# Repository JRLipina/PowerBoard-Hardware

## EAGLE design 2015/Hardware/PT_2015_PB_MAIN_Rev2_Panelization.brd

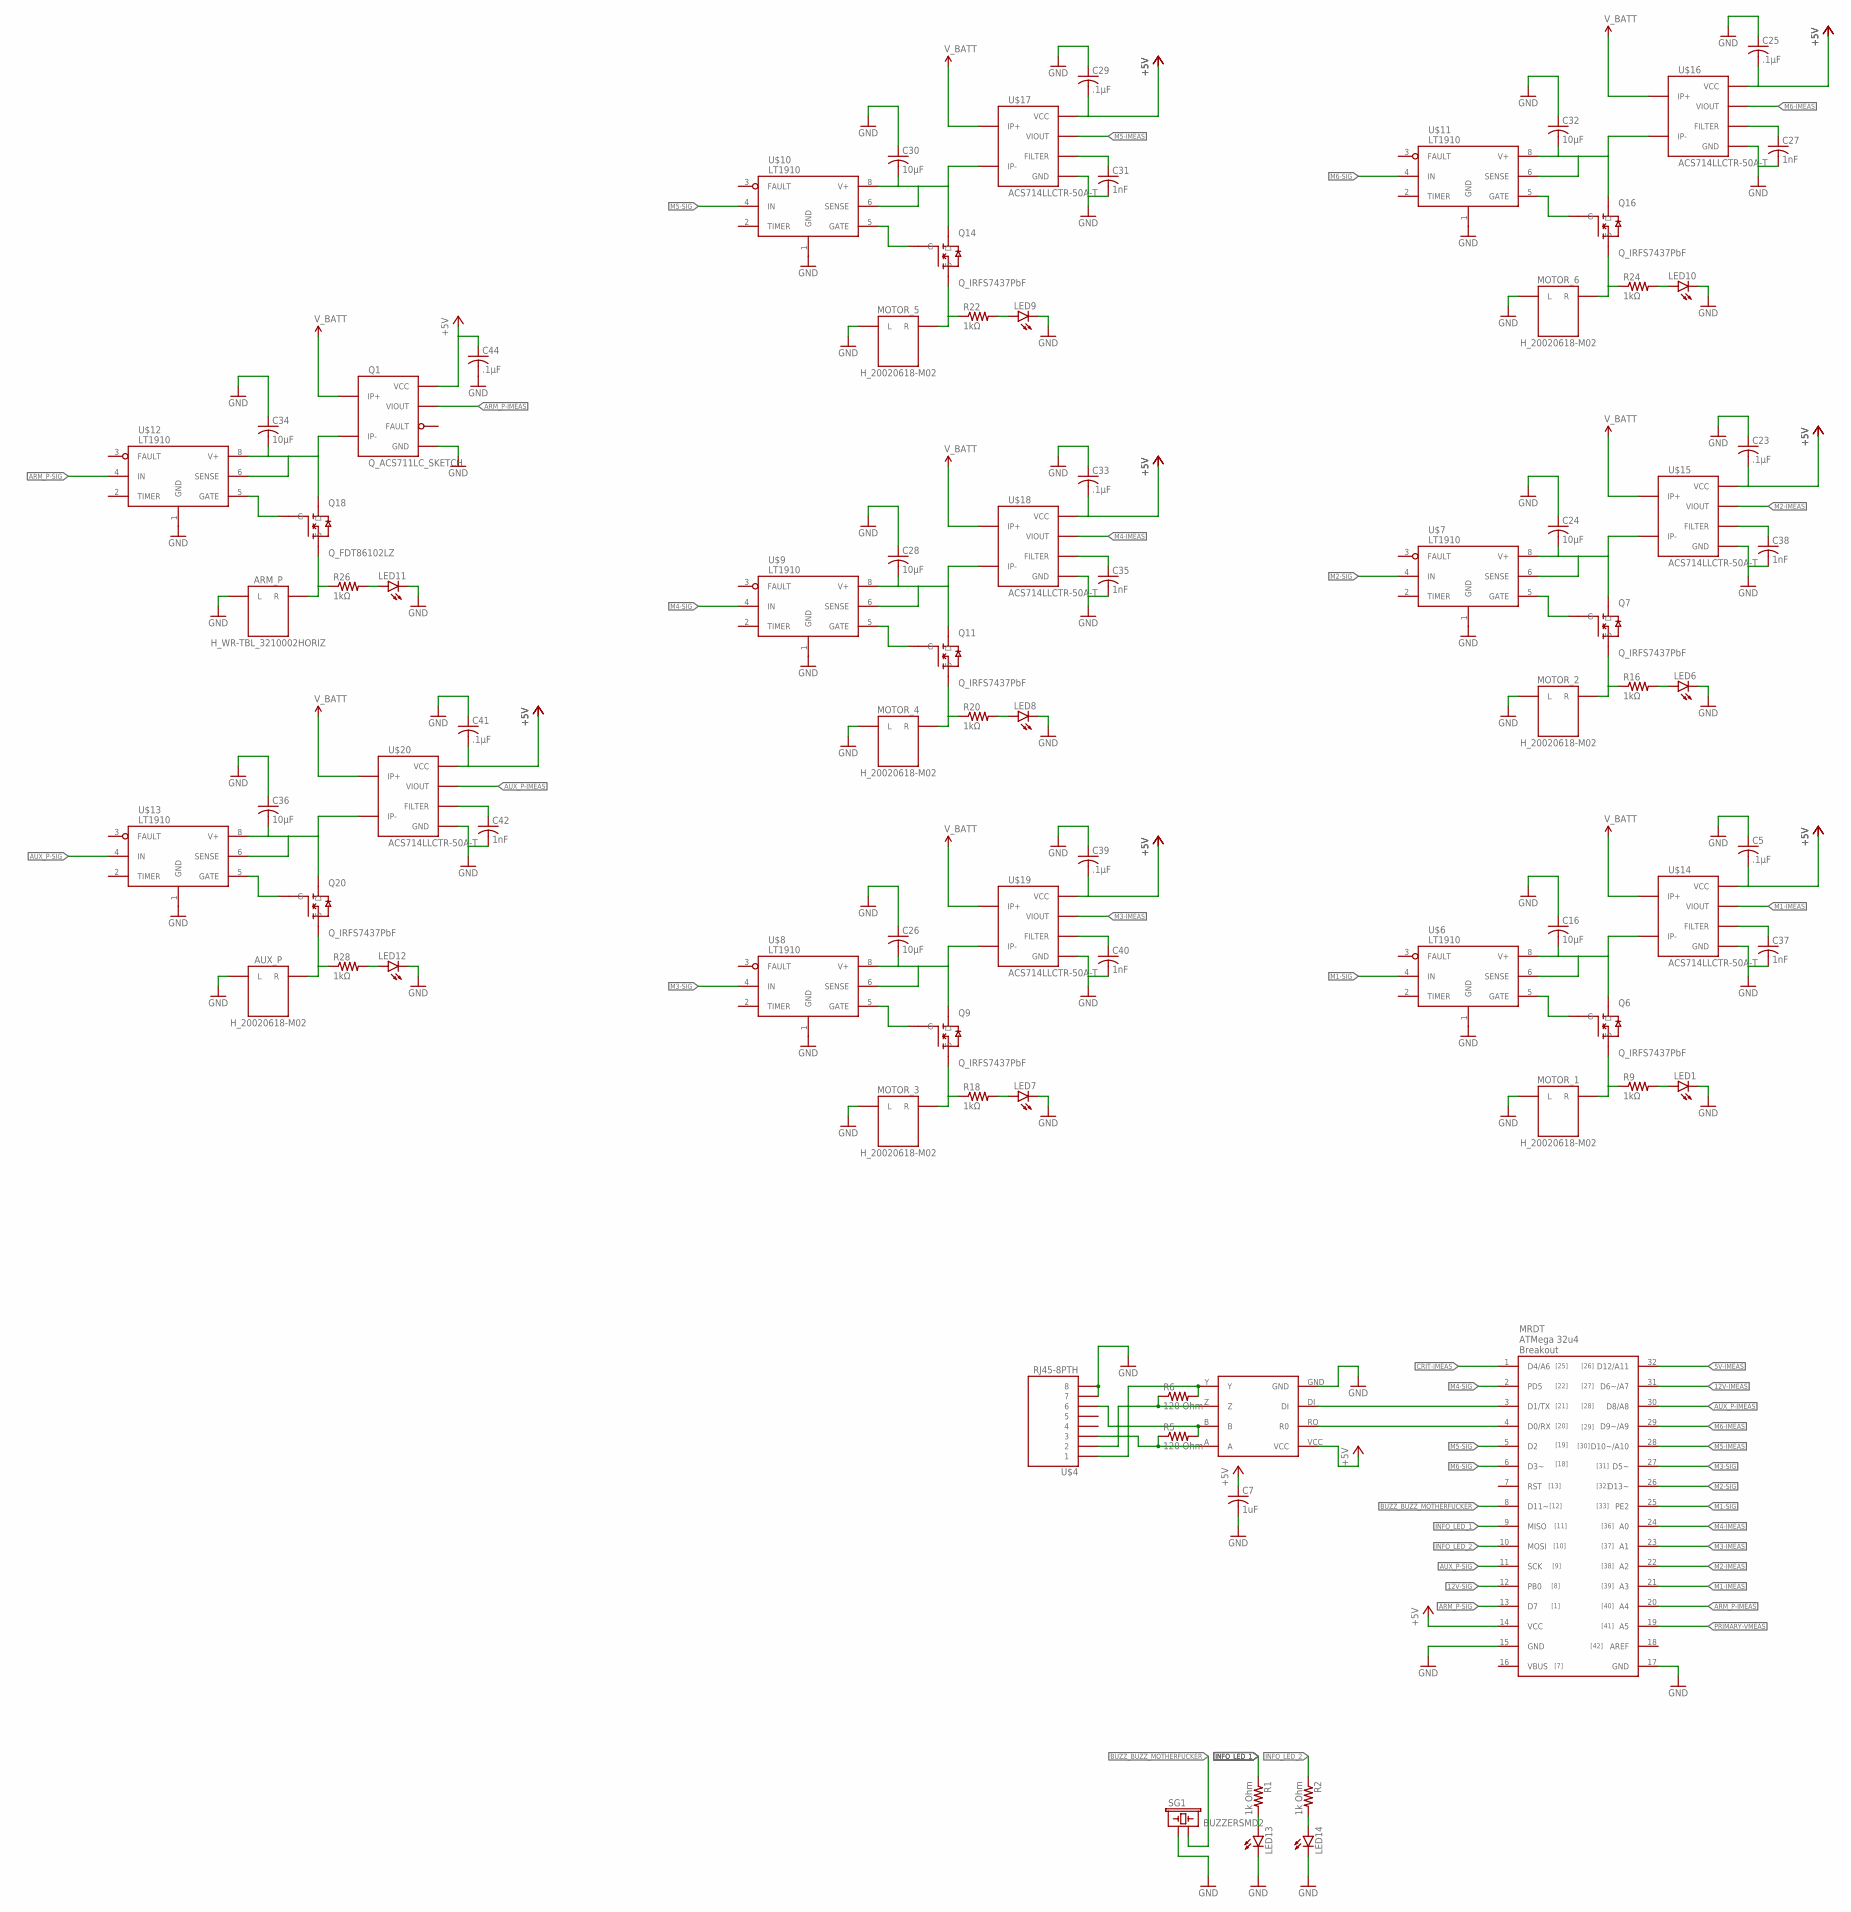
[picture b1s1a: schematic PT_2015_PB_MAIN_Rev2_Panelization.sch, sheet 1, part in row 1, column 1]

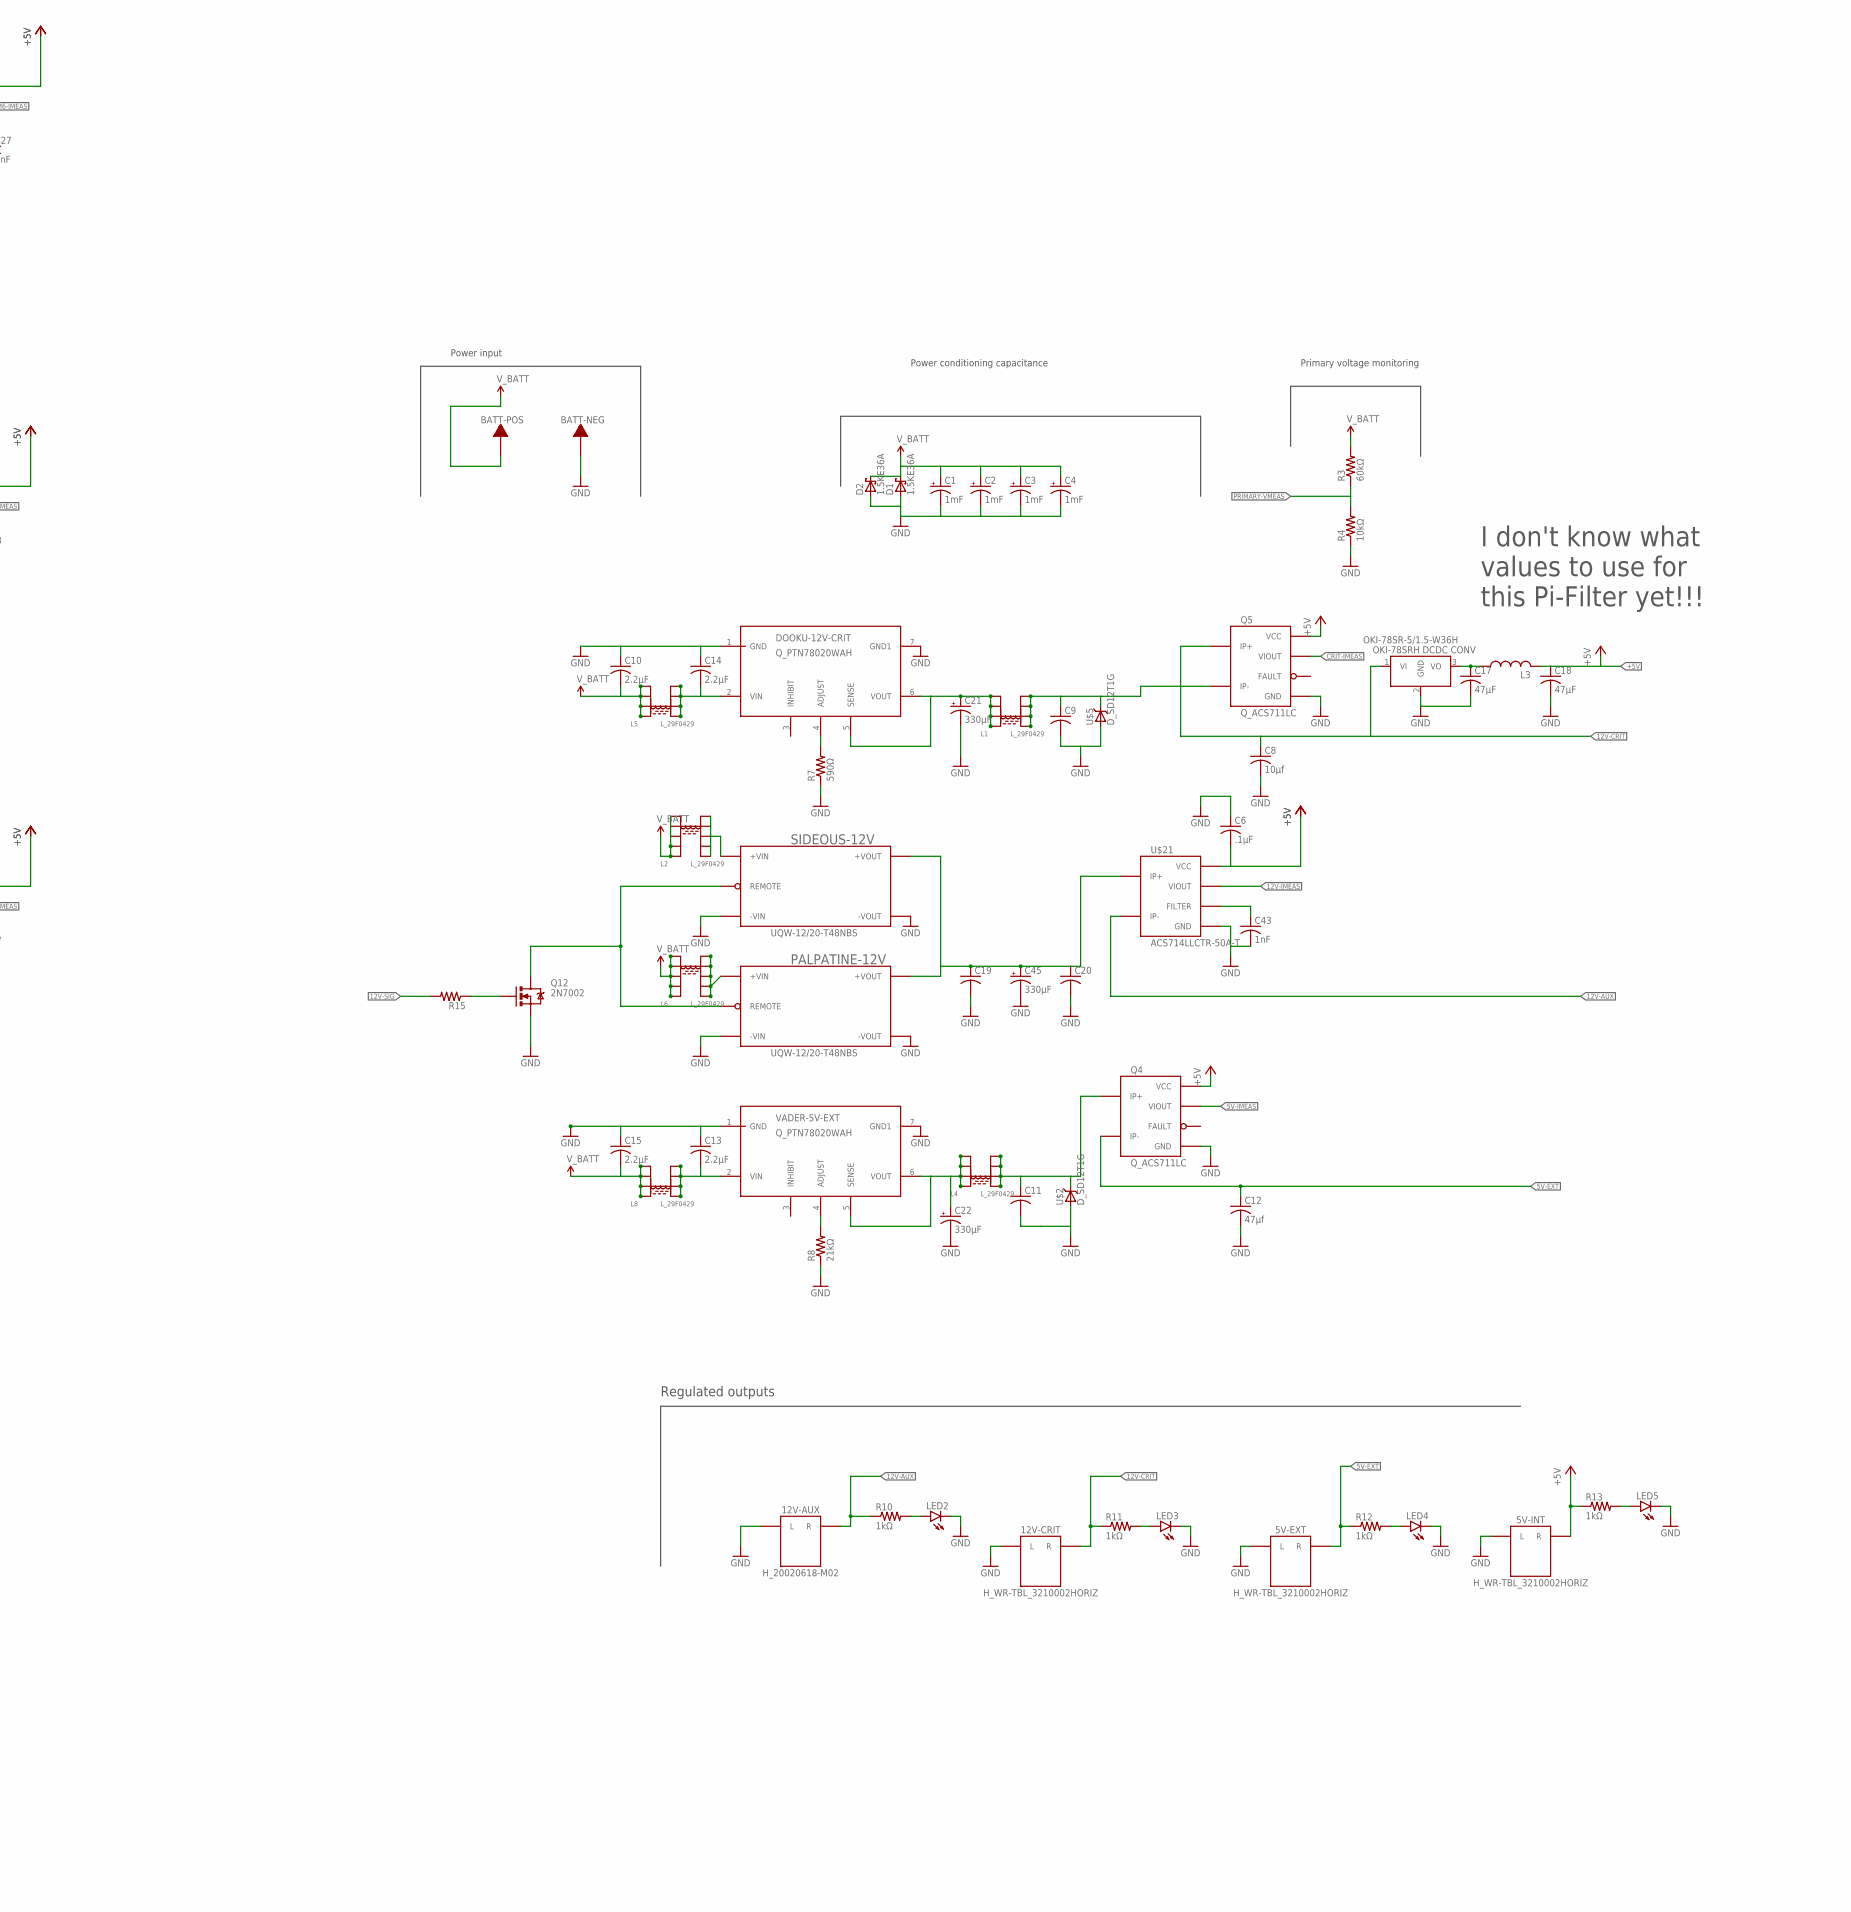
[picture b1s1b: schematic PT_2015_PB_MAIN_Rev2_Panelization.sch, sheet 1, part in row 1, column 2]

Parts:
5V-EXT, 5V-INT, 12V-CRIT: H_WR-TBL_3210002HORIZ; 691322110002
12V-AUX: H_20020618-M02; 20020618-M02
ARM_P: H_WR-TBL_3210002HORIZ; 691322110002
AUX_P: H_20020618-M02; 20020618-M02
BATT-NEG: TERMINAL_HOLE; LARGE_TERMINAL_HOLE
BATT-POS: TERMINAL_HOLE; LARGE_TERMINAL_HOLE
C1, C2, C3, C4: 1mF; C_12.5MM
C5, C6, C23, C25, C29, C33, C39, C41, C44: .1µF; C1206
C7: 1uF; C1206
C8: 10µf; C1206
C9, C11, C19, C20: C-USC1206; C1206
C10, C13, C14, C15: 2.2µF; C1206
C12: 47µf; C1206
C16, C24, C26, C28, C30, C32, C34, C36: 10µF; C1206
C17, C18: 47µF; C1206
C21, C22, C45: 330µF; E5-8,5
C27, C31, C35, C37, C38, C40, C42, C43: 1nF; C0805
D1, D2: 1.5KE36A; CB429-17
DOOKU-12V-CRIT: Q_PTN78020WAH; R_PDSS-T7
L1, L4, L5, L8: L_29F0429
L2, L6: L_29F0429; L_29F0528
L3: L-USL4532C; L4532M
LED1, LED2, LED3, LED4, LED5, LED6, LED7, LED8, LED9, LED10, LED11, LED12: LED1206; LED-1206
LED13, LED14: LED-FKIT-1206; FKIT-LED-1206
MOTOR_1, MOTOR_2, MOTOR_3, MOTOR_4, MOTOR_5, MOTOR_6: H_20020618-M02; 20020618-M02
OKI-78SR-5/1.5-W36H: Q_OKI-78SR; OKI-78SRH
PALPATINE-12V: UQW-12/20-T48NBS; U-T48-QB-NO_TRIM
Q1: Q_ACS711LC_SKETCH; SOIC8_ACS711_SKETCH
Q4, Q5: Q_ACS711LC; SOIC8_ACS711
Q6, Q7, Q9, Q11, Q14, Q16, Q20: Q_IRFS7437PbF; D2PACK
Q12: 2N7002; SOT323
Q18: Q_FDT86102LZ; SOT-223
R1, R2: 1k Ohm; 1206
R3: 60kΩ; R1206
R4: 10kΩ; R1206
R5, R6: 120 Ohm; 1206
R7: 590Ω; R1206
R8: 21kΩ; R1206
R9, R10, R11, R12, R13, R16, R18, R20, R22, R24, R26, R28: 1kΩ; 1206
R15: R-US_R1206; R1206
SG1: BUZZERSMD2; BUZZER-CCV
SIDEOUS-12V: UQW-12/20-T48NBS; U-T48-QB-NO_TRIM
U$1: 32U4_BREAKOUT; 32U4_MCU_DIP
U$2, U$5: D_SD12T1G; SOD-323
U$3: MAX3077; MAX3070E
U$4: RJ45-8PTH; RJ45-8
U$6, U$7, U$8, U$9, U$10, U$11, U$12, U$13: LT1910; SO8
U$14, U$15, U$16, U$17, U$18, U$19, U$20: ACS714LLCTR-50A-T; SOIC8_ACS711_SKETCH
U$21: ACS714LLCTR-50A-T; SOIC8_ACS711
VADER-5V-EXT: Q_PTN78020WAH; R_PDSS-T7

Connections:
0: 5V-EXT.L, 5V-INT.L, 12V-AUX.L1 (L), 12V-AUX.L2 (L), 12V-CRIT.L, ARM_P.L, AUX_P.L1 (L), AUX_P.L2 (L), BATT-NEG.P$1, C1.-, C2.-, C3.-, C4.-, C5.1, C6.1, C7.2, C8.2, C9.2, C10.1, C11.2, C12.2, C13.1, C14.1, C15.1, C16.1, C17.2, C18.2, C19.2, C20.2, C21.-, C22.-, C23.1, C24.1, C25.1, C26.1, C27.2, C28.1, C29.1, C30.1, C31.2, C32.1, C33.1, C34.1, C35.2, C36.1, C37.2, C38.2, C39.1, C40.2, C41.1, C42.2, C43.2, C44.2, C45.-, D1.A, D2.A, DOOKU-12V-CRIT.1 (GND), DOOKU-12V-CRIT.7 (GND1), LED1.C, LED2.C, LED3.C, LED4.C, LED5.C, LED6.C, LED7.C, LED8.C, LED9.C, LED10.C, LED11.C, LED12.C, LED13.C, LED14.C, MOTOR_1.L1 (L), MOTOR_1.L2 (L), MOTOR_2.L1 (L), MOTOR_2.L2 (L), MOTOR_3.L1 (L), MOTOR_3.L2 (L), MOTOR_4.L1 (L), MOTOR_4.L2 (L), MOTOR_5.L1 (L), MOTOR_5.L2 (L), MOTOR_6.L1 (L), MOTOR_6.L2 (L), OKI-78SR-5/1.5-W36H.2 (GND), PALPATINE-12V.3 (-VIN), PALPATINE-12V.4 (-VOUT), Q1.5 (GND), Q4.5 (GND), Q5.5 (GND), Q12.2 (S), R4.1, R7.1, R8.1, SG1.+ (1), SIDEOUS-12V.3 (-VIN), SIDEOUS-12V.4 (-VOUT), U$1.15 (GND), U$1.17 (GND), U$2.2 (A), U$3.GND, U$4.7, U$4.8, U$5.2 (A), U$6.1 (GND), U$7.1 (GND), U$8.1 (GND), U$9.1 (GND), U$10.1 (GND), U$11.1 (GND), U$12.1 (GND), U$13.1 (GND), U$14.5 (GND), U$15.5 (GND), U$16.5 (GND), U$17.5 (GND), U$18.5 (GND), U$19.5 (GND), U$20.5 (GND), U$21.5 (GND), VADER-5V-EXT.1 (GND), VADER-5V-EXT.7 (GND1)
5V-EXT: 5V-EXT.R, C12.1, Q4.4 (IP-), R12.1
5V-IMEAS: Q4.7 (VIOUT), U$1.32 (D12/A11)
12V-AUX: 12V-AUX.R1 (R), 12V-AUX.R2 (R), R10.1, U$21.4 (IP-)
12V-CRIT: 12V-CRIT.R, C8.1, OKI-78SR-5/1.5-W36H.1 (VI), Q5.1 (IP+), R11.1
12V-IMEAS: U$1.31 (D6~/A7), U$21.7 (VIOUT)
12V-SIG: R15.2, U$1.12 (PB0)
+5V: 5V-INT.R, C5.2, C6.2, C7.1, C18.1, C23.2, C25.2, C29.2, C33.2, C39.2, C41.2, C44.1, L3.2, Q1.8 (VCC), Q4.8 (VCC), Q5.8 (VCC), R13.1, U$1.14 (VCC), U$3.VCC, U$14.8 (VCC), U$15.8 (VCC), U$16.8 (VCC), U$17.8 (VCC), U$18.8 (VCC), U$19.8 (VCC), U$20.8 (VCC), U$21.8 (VCC)
ARM_P-IMEAS: Q1.7 (VIOUT), U$1.20 (A4)
ARM_P-SIG: U$1.13 (D7), U$12.4 (IN)
AUX_P-IMEAS: U$1.30 (D8/A8), U$20.7 (VIOUT)
AUX_P-SIG: U$1.11 (SCK), U$13.4 (IN)
BUZZ_BUZZ_MOTHERFUCKER: SG1.- (2), U$1.8 (D11~)
CRIT-IMEAS: Q5.7 (VIOUT), U$1.1 (D4/A6)
INFO_LED_1: R1.1, U$1.9 (MISO)
INFO_LED_2: R2.1, U$1.10 (MOSI)
M1-IMEAS: U$1.21 (A3), U$14.7 (VIOUT)
M1-SIG: U$1.25 (PE2), U$6.4 (IN)
M2-IMEAS: U$1.22 (A2), U$15.7 (VIOUT)
M2-SIG: U$1.26 (D13~), U$7.4 (IN)
M3-IMEAS: U$1.23 (A1), U$19.7 (VIOUT)
M3-SIG: U$1.27 (D5~), U$8.4 (IN)
M4-IMEAS: U$1.24 (A0), U$18.7 (VIOUT)
M4-SIG: U$1.2 (PD5), U$9.4 (IN)
M5-IMEAS: U$1.28 (D10~/A10), U$17.7 (VIOUT)
M5-SIG: U$1.5 (D2), U$10.4 (IN)
M6-IMEAS: U$1.29 (D9~/A9), U$16.7 (VIOUT)
M6-SIG: U$1.6 (D3~), U$11.4 (IN)
unnamed: C37.1, U$14.6 (FILTER)
unnamed: C38.1, U$15.6 (FILTER)
unnamed: C13.2, L8.5, L8.6, L8.7, L8.8, VADER-5V-EXT.2 (VIN)
unnamed: PALPATINE-12V.2 (REMOTE), Q12.3 (D), SIDEOUS-12V.2 (REMOTE)
unnamed: L6.6, L6.7, L6.8, L6.9, L6.10, PALPATINE-12V.1 (+VIN)
unnamed: L2.6, L2.7, L2.8, L2.9, L2.10, SIDEOUS-12V.1 (+VIN)
unnamed: C19.1, C20.1, C45.+, PALPATINE-12V.8 (+VOUT), SIDEOUS-12V.8 (+VOUT), U$21.1 (IP+)
unnamed: C14.2, DOOKU-12V-CRIT.2 (VIN), L5.5, L5.6, L5.7, L5.8
unnamed: DOOKU-12V-CRIT.4 (ADJUST), R7.2
unnamed: C9.1, L1.5, L1.6, L1.7, L1.8, Q5.4 (IP-), U$5.1 (C)
unnamed: LED13.A, R1.2
unnamed: C43.1, U$21.6 (FILTER)
unnamed: R6.2, U$3.Y, U$4.1
unnamed: C22.+, L4.1, L4.2, L4.3, L4.4, VADER-5V-EXT.5 (SENSE), VADER-5V-EXT.6 (VOUT)
unnamed: C11.1, L4.5, L4.6, L4.7, L4.8, Q4.1 (IP+), U$2.1 (C)
unnamed: C27.1, U$16.6 (FILTER)
unnamed: R6.1, U$3.Z, U$4.2
unnamed: R5.2, U$3.B, U$4.6
unnamed: R5.1, U$3.A, U$4.3
unnamed: U$1.3 (D1/TX), U$3.DI
unnamed: C31.1, U$17.6 (FILTER)
unnamed: C35.1, U$18.6 (FILTER)
unnamed: C40.1, U$19.6 (FILTER)
unnamed: C42.1, U$20.6 (FILTER)
unnamed: C24.2, Q7.TAB (D), U$7.6 (SENSE), U$7.8 (V+), U$15.4 (IP-)
unnamed: MOTOR_2.R1 (R), MOTOR_2.R2 (R), Q7.2 (S), R16.1
unnamed: Q7.1 (G), U$7.5 (GATE)
unnamed: LED6.A, R16.2
unnamed: LED14.A, R2.2
unnamed: R8.2, VADER-5V-EXT.4 (ADJUST)
unnamed: C21.+, DOOKU-12V-CRIT.5 (SENSE), DOOKU-12V-CRIT.6 (VOUT), L1.1, L1.2, L1.3, L1.4
unnamed: LED1.A, R9.2
unnamed: C16.2, Q6.TAB (D), U$6.6 (SENSE), U$6.8 (V+), U$14.4 (IP-)
unnamed: MOTOR_1.R1 (R), MOTOR_1.R2 (R), Q6.2 (S), R9.1
unnamed: Q6.1 (G), U$6.5 (GATE)
unnamed: C26.2, Q9.TAB (D), U$8.6 (SENSE), U$8.8 (V+), U$19.4 (IP-)
unnamed: MOTOR_3.R1 (R), MOTOR_3.R2 (R), Q9.2 (S), R18.1
unnamed: LED2.A, R10.2
unnamed: Q9.1 (G), U$8.5 (GATE)
unnamed: LED3.A, R11.2
unnamed: LED7.A, R18.2
unnamed: LED4.A, R12.2
unnamed: LED5.A, R13.2
unnamed: C28.2, Q11.TAB (D), U$9.6 (SENSE), U$9.8 (V+), U$18.4 (IP-)
unnamed: MOTOR_4.R1 (R), MOTOR_4.R2 (R), Q11.2 (S), R20.1
unnamed: Q11.1 (G), U$9.5 (GATE)
unnamed: LED8.A, R20.2
unnamed: C30.2, Q14.TAB (D), U$10.6 (SENSE), U$10.8 (V+), U$17.4 (IP-)
unnamed: MOTOR_5.R1 (R), MOTOR_5.R2 (R), Q14.2 (S), R22.1
unnamed: Q14.1 (G), U$10.5 (GATE)
unnamed: LED9.A, R22.2
unnamed: C32.2, Q16.TAB (D), U$11.6 (SENSE), U$11.8 (V+), U$16.4 (IP-)
unnamed: MOTOR_6.R1 (R), MOTOR_6.R2 (R), Q16.2 (S), R24.1
unnamed: Q16.1 (G), U$11.5 (GATE)
unnamed: LED10.A, R24.2
unnamed: C34.2, Q1.4 (IP-), Q18.2 (D), Q18.4 (D), U$12.6 (SENSE), U$12.8 (V+)
unnamed: ARM_P.R, Q18.3 (S), R26.1
unnamed: Q18.1 (G), U$12.5 (GATE)
unnamed: LED11.A, R26.2
unnamed: C36.2, Q20.TAB (D), U$13.6 (SENSE), U$13.8 (V+), U$20.4 (IP-)
unnamed: AUX_P.R1 (R), AUX_P.R2 (R), Q20.2 (S), R28.1
unnamed: Q20.1 (G), U$13.5 (GATE)
unnamed: LED12.A, R28.2
unnamed: C17.1, L3.1, OKI-78SR-5/1.5-W36H.3 (VO)
unnamed: Q12.1 (G), R15.1
PRIMARY-VMEAS: R3.1, R4.2, U$1.19 (A5)
RXD: U$1.4 (D0/RX), U$3.RO (R0)
V_BATT: BATT-POS.P$1, C1.+, C2.+, C3.+, C4.+, C10.2, C15.2, D1.C, D2.C, L2.1, L2.2, L2.3, L2.4, L2.5, L5.1, L5.2, L5.3, L5.4, L6.1, L6.2, L6.3, L6.4, L6.5, L8.1, L8.2, L8.3, L8.4, Q1.1 (IP+), R3.2, U$14.1 (IP+), U$15.1 (IP+), U$16.1 (IP+), U$17.1 (IP+), U$18.1 (IP+), U$19.1 (IP+), U$20.1 (IP+)

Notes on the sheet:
Primary voltage monitoring
Power conditioning capacitance
Power input
I don't know what values to use for this Pi-Filter yet!!!
Regulated outputs

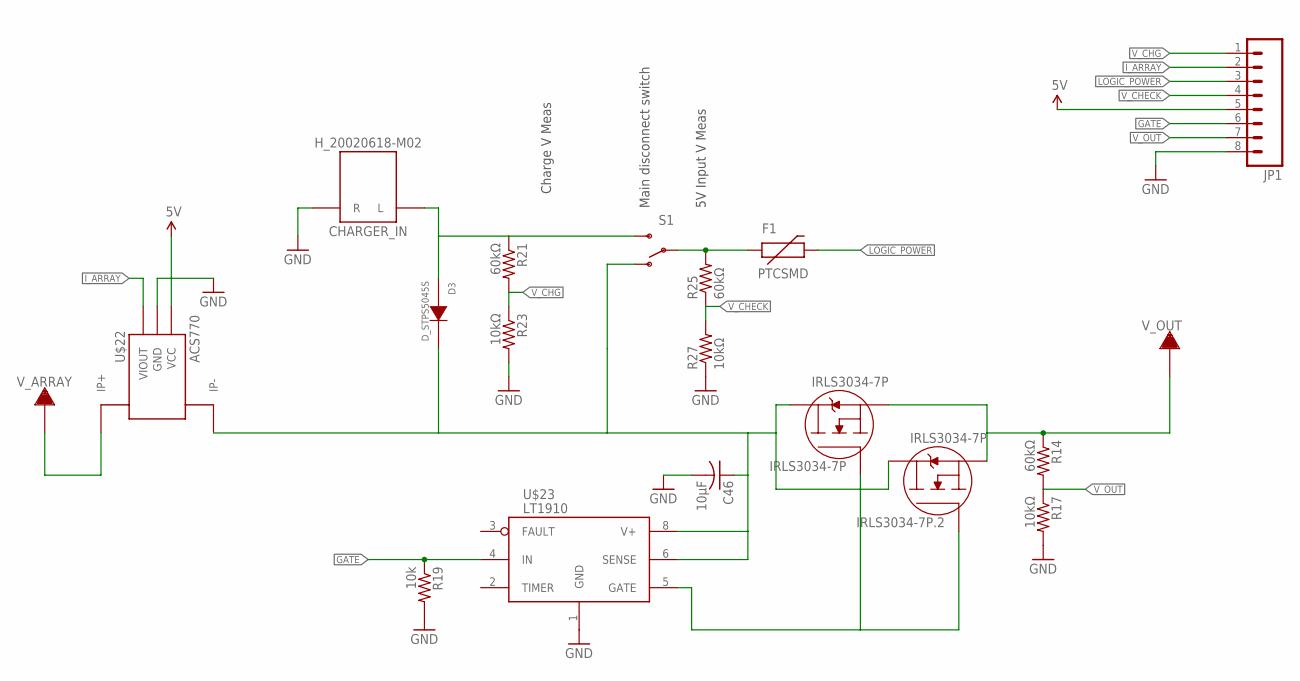
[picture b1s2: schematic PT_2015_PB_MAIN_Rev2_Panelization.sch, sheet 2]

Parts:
C46: 10µF; C1206
CHARGER_IN: H_20020618-M02; 20020618-M02
D3: D_STPS5045S; D2PACK
F1: PTCSMD; PTC-1206
IRLS3034-7P, IRLS3034-7P.2: IRLS3034-7P; D2PAK-7
JP1: M08BM08B-SRSS-TB; BM08B-SRSS-TB
R14, R21, R25: 60kΩ; R1206
R17, R23, R27: 10kΩ; R1206
R19: 10k; R1206
S1: SWITCH-SPDTPTH; SWITCH-SPDT
U$22: ACS770; PFF_LEADFORM
U$23: LT1910; SO8
V_ARRAY: TERMINAL_HOLE; LARGE_TERMINAL_HOLE
V_OUT: TERMINAL_HOLE; LARGE_TERMINAL_HOLE

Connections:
5V_SSR: JP1.5, U$22.1 (VCC)
GATE: JP1.6, R19.1, U$23.4 (IN)
GND_SSR: C46.2, CHARGER_IN.R1 (R), CHARGER_IN.R2 (R), JP1.8, R17.2, R19.2, R23.2, R27.1, U$22.2 (GND), U$23.1 (GND)
I_ARRAY: JP1.2, U$22.3 (VIOUT)
LOGIC_POWER: F1.2, JP1.3
unnamed: IRLS3034-7P.2 (SOURCE), IRLS3034-7P.3 (SOURCE), IRLS3034-7P.4 (SOURCE), IRLS3034-7P.5 (SOURCE), IRLS3034-7P.6 (SOURCE), IRLS3034-7P.2.2 (SOURCE), IRLS3034-7P.2.3 (SOURCE), IRLS3034-7P.2.4 (SOURCE), IRLS3034-7P.2.5 (SOURCE), IRLS3034-7P.2.6 (SOURCE), R14.1, V_OUT.P$1
unnamed: IRLS3034-7P.1 (GATE), IRLS3034-7P.2.1 (GATE), U$23.5 (GATE)
unnamed: U$22.4_1 (IP+), U$22.4_2 (IP+), U$22.4_3 (IP+), U$22.4_4 (IP+), U$22.4_5 (IP+), U$22.4_6 (IP+), U$22.4_7 (IP+), U$22.4_8 (IP+), U$22.4_9 (IP+), U$22.4_10 (IP+), U$22.4_11 (IP+), U$22.4_12 (IP+), U$22.4_13 (IP+), U$22.4_14 (IP+), U$22.4_15 (IP+), U$22.4_16 (IP+), U$22.4_B (IP+), U$22.4_T (IP+), V_ARRAY.P$1
unnamed: C46.1, D3.TAB (K), IRLS3034-7P.PAD (DRAIN), IRLS3034-7P.2.PAD (DRAIN), S1.1 (O), U$22.5_1 (IP-), U$22.5_2 (IP-), U$22.5_3 (IP-), U$22.5_4 (IP-), U$22.5_5 (IP-), U$22.5_6 (IP-), U$22.5_7 (IP-), U$22.5_8 (IP-), U$22.5_9 (IP-), U$22.5_10 (IP-), U$22.5_11 (IP-), U$22.5_12 (IP-), U$22.5_13 (IP-), U$22.5_14 (IP-), U$22.5_15 (IP-), U$22.5_16 (IP-), U$22.5_B (IP-), U$22.5_T (IP-), U$23.6 (SENSE), U$23.8 (V+)
unnamed: CHARGER_IN.L1 (L), CHARGER_IN.L2 (L), D3.1 (A), D3.2 (A), R21.1, S1.3 (S)
unnamed: F1.1, R25.2, S1.2
V_CHECK: JP1.4, R25.1, R27.2
V_CHG: JP1.1, R21.2, R23.1
V_OUT: JP1.7, R14.2, R17.1

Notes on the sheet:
Charge V Meas
5V Input V Meas
Main disconnect switch

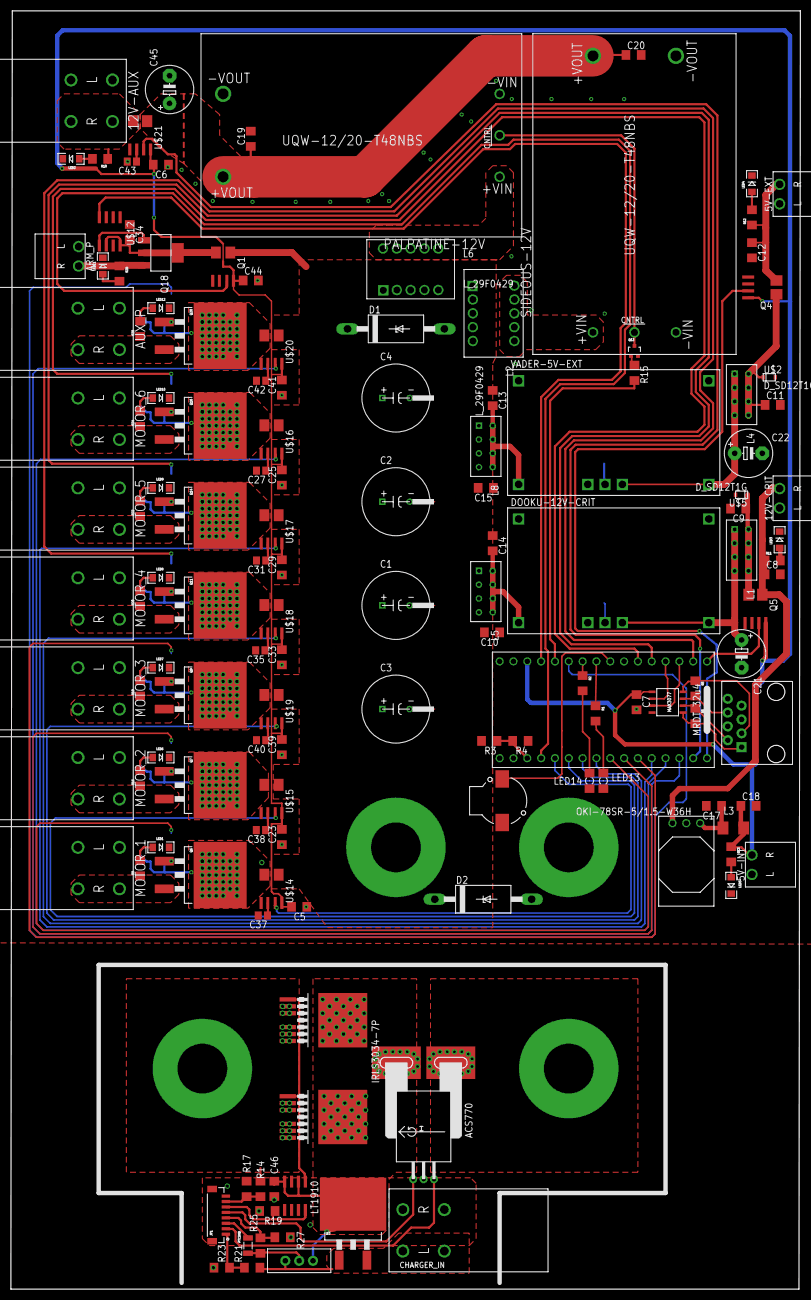
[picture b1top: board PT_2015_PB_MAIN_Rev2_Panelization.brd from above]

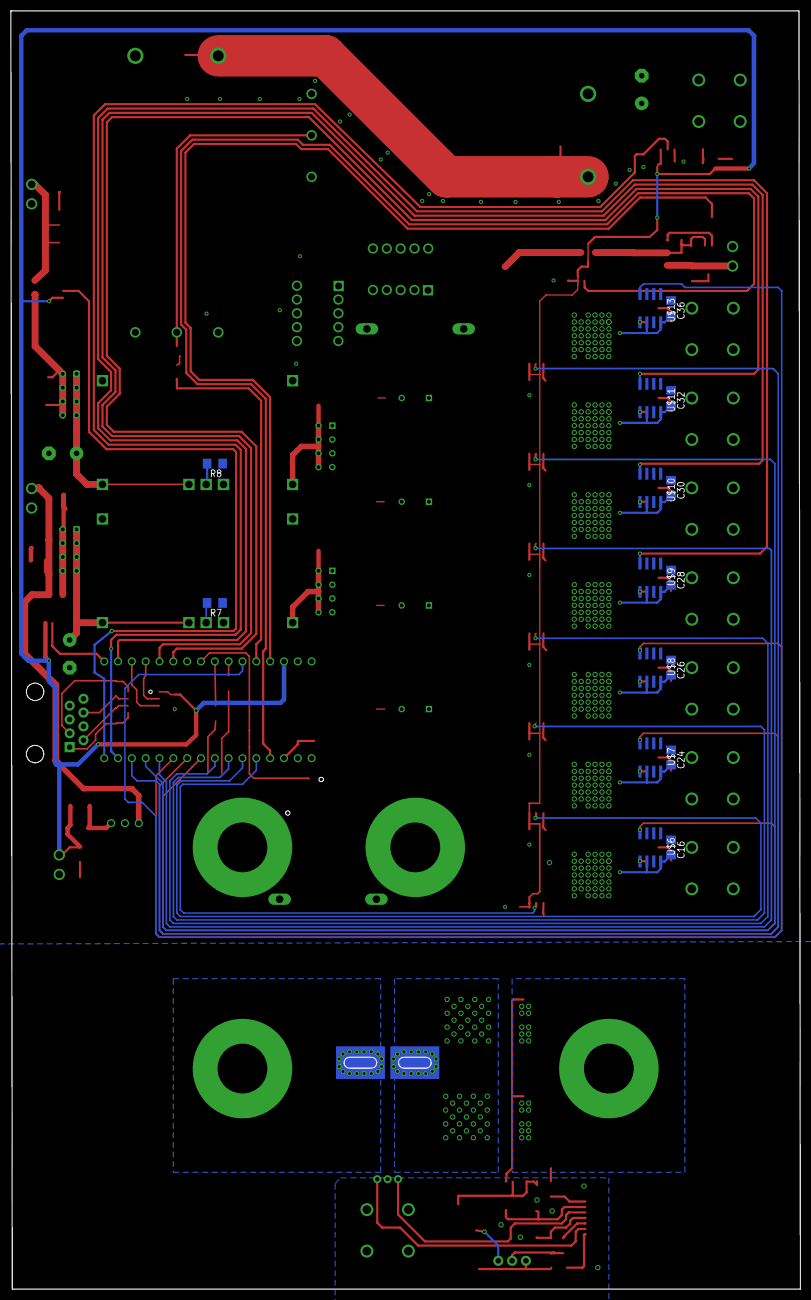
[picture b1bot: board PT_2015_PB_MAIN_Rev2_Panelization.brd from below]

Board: 2 copper layers, 145.0 x 234.8 mm, 161 parts (16 on the bottom side), 110 nets.

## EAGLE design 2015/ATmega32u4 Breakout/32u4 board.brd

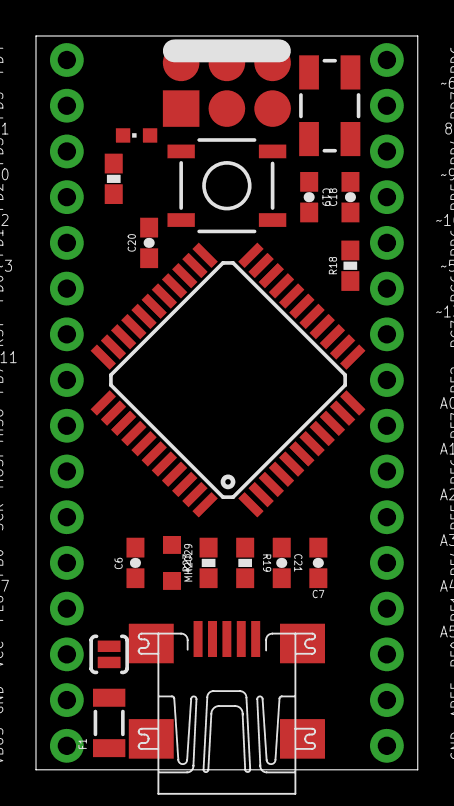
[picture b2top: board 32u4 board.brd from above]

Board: 2 copper layers, 21.2 x 40.8 mm, 21 parts (0 on the bottom side), 41 nets, no tracks yet.

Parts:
C6: 1uF; 0603-CAP
C7: 1.0uF; 0603-CAP
C18, C19: 18pF; 0603-CAP
C20, C21: 0.1uF; 0603-CAP
F1: PTCSMD; PTC-1206
JP1, JP2: M161X16_NO_SILK; 1X16_NO_SILK
LED1: CHIPLED_0603
MH2029: MH2029-300Y; L2012C
R1: 1k; 0603-RES
R18: 10k; 0603-RES
R19, R23: 22; 0603-RES
S1: SWITCH-MOMENTARY-2SMD; TACTILE_SWITCH_SMD
SJ1: SOLDERJUMPERNO; SJ_2S-NO
U$2: ICSP_SMD; ICSP
U$3: ATMEGA32U4TQFP-44; TQFP44
U$4: CRYSTAL-GROUNDED; CRYSTAL-SMD-5X3
X1: MINI-USB-UX60A-MB-5ST; UX60A-MB-5ST

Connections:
AREF: C21.1, JP1.15, U$3.42
D+: R19.2, X1.3
D-: R23.2, X1.2
GND: C6.2, C7.2, C18.2, C19.2, C20.2, C21.2, JP1.16, JP2.2, R1.1, S1.1, U$2.3, U$3.5, U$3.15, U$3.23, U$3.35, U$3.43, U$4.2, U$4.4, X1.5
MISO: JP2.8, U$2.6, U$3.11
MOSI: JP2.7, U$2.2, U$3.10
unnamed: LED1.C, R1.2
unnamed: F1.2, X1.1
unnamed: R19.1, U$3.4
unnamed: R23.1, U$3.3
unnamed: C6.1, U$3.6
unnamed: C20.1, MH2029.1, U$3.24, U$3.44
unnamed: C19.1, U$3.17, U$4.3
unnamed: C18.1, U$3.16, U$4.1
PB0: JP2.5, U$3.8
PB4: JP1.3, U$3.28
PB5: JP1.4, U$3.29
PB6: JP1.5, U$3.30
PB7: JP2.9, U$3.12
PC6: JP1.6, U$3.31
PC7: JP1.7, U$3.32
PD0: JP2.11, U$3.18
PD1: JP2.12, U$3.19
PD2: JP2.13, U$3.20
PD3: JP2.14, U$3.21
PD4: JP2.16, U$3.25
PD5: JP2.15, U$3.22
PD6: JP1.1, U$3.26
PD7: JP1.2, U$3.27
PE2: JP1.8, U$3.33
PE6: JP2.4, U$3.1
PF0: JP1.14, U$3.41
PF1: JP1.13, U$3.40
PF4: JP1.12, U$3.39
PF5: JP1.11, U$3.38
PF6: JP1.10, U$3.37
PF7: JP1.9, U$3.36
RST: JP2.10, R18.1, S1.3, U$2.4, U$3.13
SCK: JP2.6, U$2.5, U$3.9
VBUS: C7.1, F1.1, JP2.1, SJ1.1, U$3.7
VCC: JP2.3, LED1.A, MH2029.2, R18.2, SJ1.2, U$2.1, U$3.2, U$3.14, U$3.34

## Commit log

2014-11-07 Initial commit of first reroute attempt
    moving small ICs and other components to board underside
2014-11-08 continued
2014-11-11 dlkgsdkjghsa
    khsighdlka
2014-11-11 i did things
    many things
2014-11-11 i did literally nothing
    yeah
2014-12-09 Added Digikey PN for C41
    duh.
2014-12-17 Started adding Castellated Edges
    http://lmgtfy.com/?q=Castellated+Edges
2015-01-27 Soldermask removed
    high current traces now have soldermask removed to thicken with solder
    for higher current capability. Must be coated with solder mask or tape
    after soldering. Need to check/verify doing this under the board mount
    connectors, diode, and caps using 1oz board - recommend using this
    revision to purchase 1oz board for testing. Final version will be 2oz.
2015-01-28 Frankensteined the two boards together. I am hoping to save money by only ordering one board and making the cut ourselves.
2015-01-28 Spaced out the boards to make it easier to cut.
2015-01-28 Fixed all of the FreeDFM errors. The Panelized board should be ready to order. I will confirm tonight and tomorrow, but the idea is that we will cut the SSR board out of the Power Board to save a ton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
2015-01-28 Fixed the Ferrite Bead Footprint
2015-01-28 Fixed the TSTOP to prevent shorts.
2015-01-28 Deleted Extraneous BOM Files
2015-01-28 Cleaned up my idiotic TSTOP
2015-01-28 Fixed the connector on SSR portion
2015-01-29 Switched out the SSR to meet 3oz Spec
2015-01-29 Fixed DRC Errors
2015-01-30 Pushing the Final SSR/PowerBoard

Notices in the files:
parts and their libraries:
SparkFun-DigitalIC: Licensing: Creative Commons ShareAlike 4.0 International - https://creativecommons.org/licenses/by-sa/4.0
SparkFun-Capacitors: Licensing: CC v3.0 Share-Alike You are welcome to use this library for commercial purposes.
